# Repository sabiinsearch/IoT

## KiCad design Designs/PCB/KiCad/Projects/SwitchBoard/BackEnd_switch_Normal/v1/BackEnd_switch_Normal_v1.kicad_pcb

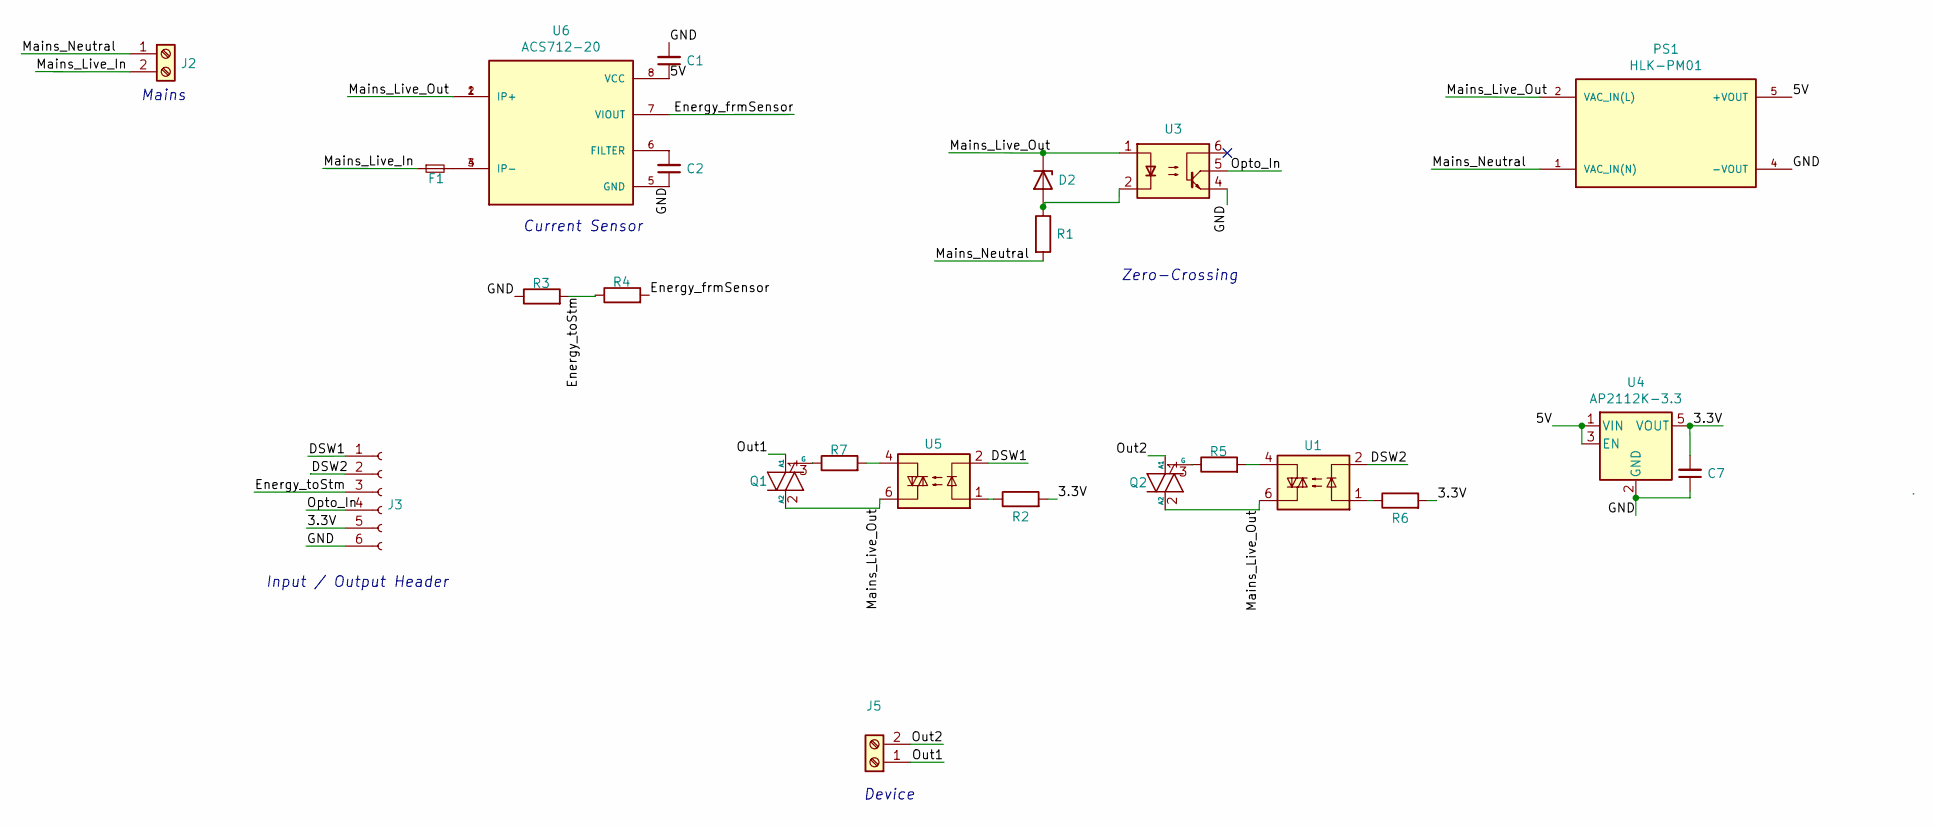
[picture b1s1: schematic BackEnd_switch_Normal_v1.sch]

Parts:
C1: 100nf; C_0805_2012Metric_Pad1.18x1.45mm_HandSolder
C2: 1nf; C_0805_2012Metric_Pad1.18x1.45mm_HandSolder
C7: 2.2uf; C_0805_2012Metric_Pad1.18x1.45mm_HandSolder
D2: IN14007; D_0805
F1: Fuse_Small; Fuse_TE5_Littlefuse-395Series
J2: Screw_Terminal_01x02; TerminalBlock_Phoenix_MKDS-1,5-2_1x02_P5.00mm_Horizontal
J3: Conn_01x06_Female; PinHeader_1x06_P2.54mm_Vertical
J5: Screw_Terminal_01x02; TerminalBlock_Phoenix_MKDS-1,5-2-5.08_1x02_P5.08mm_Horizont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
PS1: HLK-PM01; 277
Q1, Q2: BT136-500; BT136S
R1: 220K; R_0805_HandSoldering
R2, R6: 100E; R_0805_2012Metric
R3, R4: 5K; R_0805_2012Metric
R5, R7: 470E; R_0805_2012Metric
U1, U5: MOC3021; OPTOCOUPLER_SMD
U3: 4N35; DIP-6_W8.89mm_SMDSocket_LongPads
U4: AP2112K-3.3; SOT-23-5_HandSoldering
U6: ACS712-20; ACS712_20; PARTREV 19

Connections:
/3.3V: C7.2, J3.5, R2.2, R6.2, U4.5 (VOUT)
/5V: C1.1, PS1.5 (+VOUT), U4.1 (VIN), U4.3 (EN), U6.8 (VCC)
/DSW1: J3.1, U5.2
/DSW2: J3.2, U1.2
/Energy_frmSensor: R4.2, U6.7 (VIOUT)
/Energy_toStm: J3.3, R3.2, R4.1
/GND: C1.2, C2.1, C7.1, J3.6, PS1.4 (-VOUT), R3.1, U3.4, U4.2 (GND), U6.5 (GND)
/Mains_Live_In: F1.1, J2.2
/Mains_Live_Out: D2.1 (K), PS1.2 (VAC_IN(L)), Q1.2 (A2), Q2.2 (A2), U1.6, U3.1, U5.6, U6.1 (IP+), U6.2 (IP+)
/Mains_Neutral: J2.1, PS1.1 (VAC_IN(N)), R1.2
/Opto_In: J3.4, U3.5
/Out1: J5.1, Q1.1 (A1)
/Out2: J5.2, Q2.1 (A1)
unnamed: C2.2, U6.6 (FILTER)
unnamed: D2.2 (A), R1.1, U3.2
unnamed: F1.2, U6.3 (IP-), U6.4 (IP-)
unnamed: Q1.3 (G), R7.1
unnamed: Q2.3 (G), R5.1
unnamed: R2.1, U5.1
unnamed: R5.2, U1.4
unnamed: R6.1, U1.1
unnamed: R7.2, U5.4

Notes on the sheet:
Mains
Current Sensor
Zero-Crossing
Input / Output Header
Device

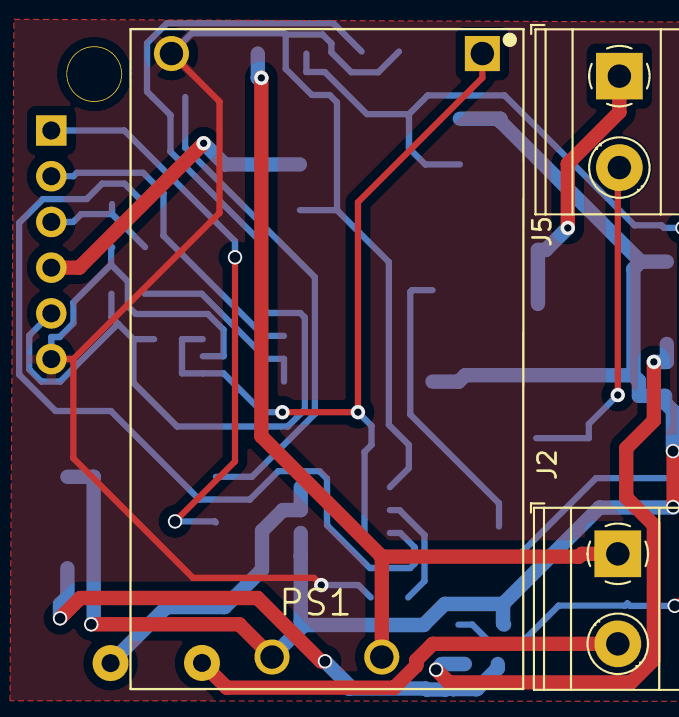
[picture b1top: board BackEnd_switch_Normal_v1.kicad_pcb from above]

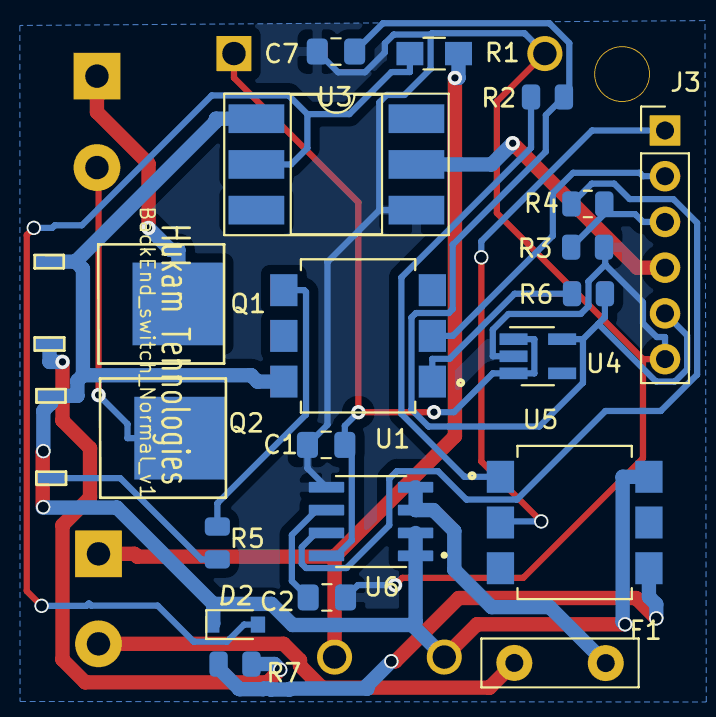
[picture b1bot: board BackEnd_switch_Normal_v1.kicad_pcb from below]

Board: 2 copper layers, 24 parts (20 on the bottom side), 22 nets.

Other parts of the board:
M2: MountingHole_2.1mm; MountingHole_2.5mm

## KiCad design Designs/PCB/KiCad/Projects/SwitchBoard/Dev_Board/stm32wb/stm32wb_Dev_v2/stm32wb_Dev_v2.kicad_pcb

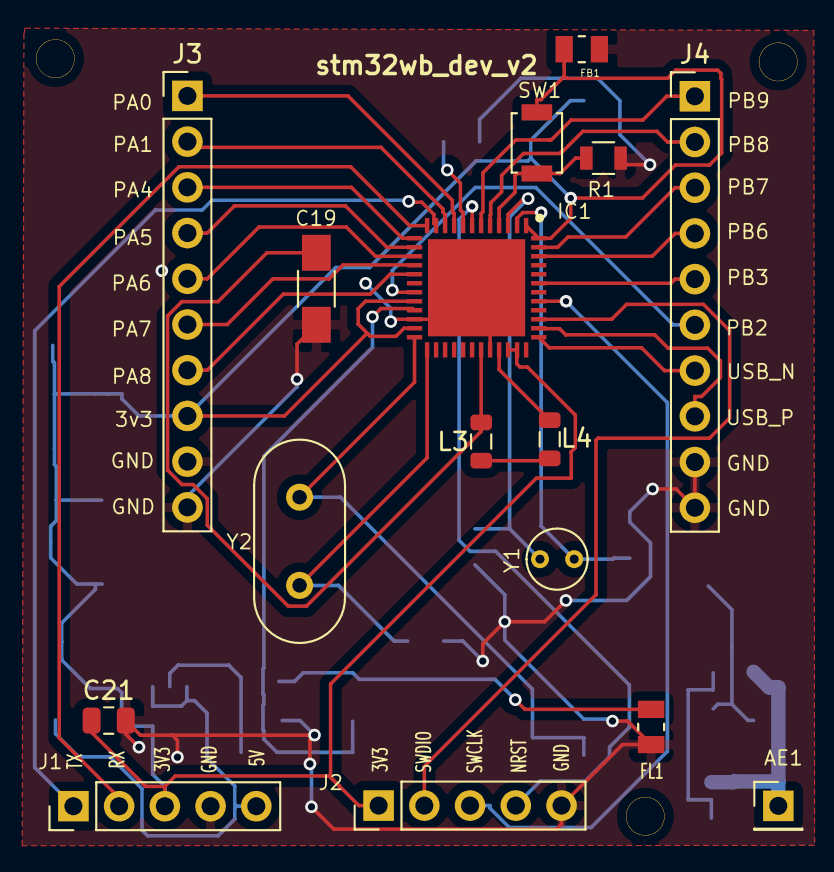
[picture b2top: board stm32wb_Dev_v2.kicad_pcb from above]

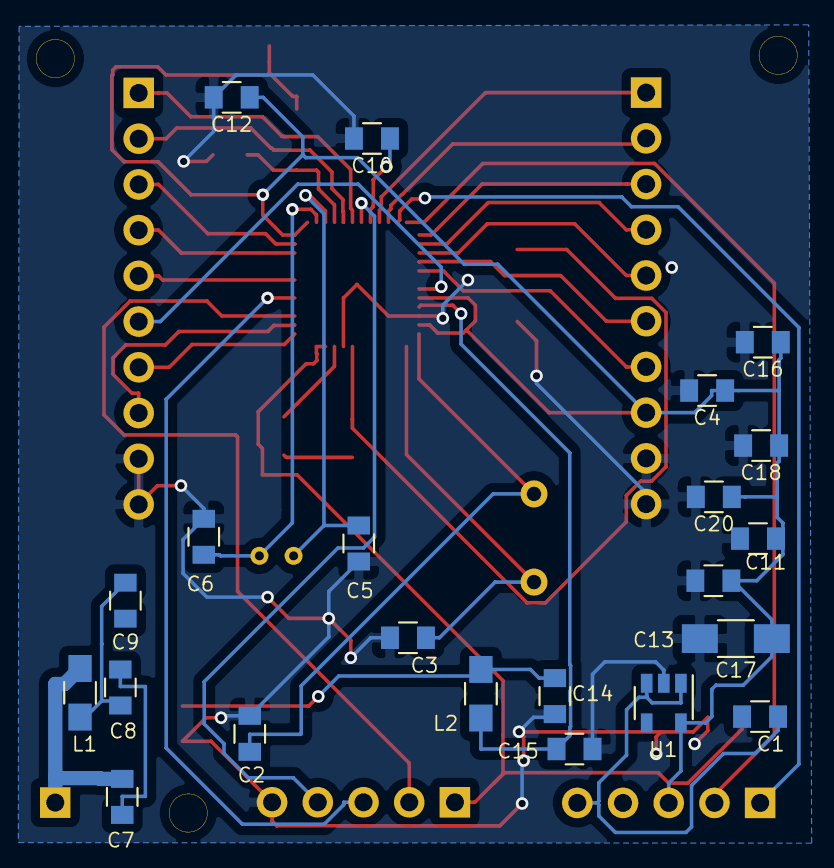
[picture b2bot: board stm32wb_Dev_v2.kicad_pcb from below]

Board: 2 copper layers, 41 parts (22 on the bottom side), 37 nets.

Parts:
AE1: Antenna; Pin_Header_Straight_1x01_Pitch2.54mm
C1, C4, C10, C12, C13, C16, C20: 100nf; C_0805
C2, C3: 22p; C_0805
C5, C6: 15pf; C_0805
C7: 1.2p; C_0805
C8: NM; C_0805
C9: 10nf; C_0805
C11, C18: 100p; C_0805
C14: 0.3p; C_0805
C15: 0.8p; C_0805
C17, C19: 4.7uf; C_1206_HandSoldering
C21: 100nf; C_0805_2012Metric
FB1: FCM1608KF-601T03; RESC0805X60N
FL1: LFB182G45CGFD436; RESC0805X60N
IC1: STM32WB55CEU6; QFN50P700X700X65-49N-D
J1, J2: Conn_01x05_Female; Pin_Header_Straight_1x05_Pitch2.54mm
J3, J4: Conn_01x10_Female; PinHeader_1x10_P2.54mm_Vertical
L1: 3.6nH; L_0805_HandSoldering
L2: 2.7nH; L_0805_HandSoldering
L3, L4: 10nH; L_0805_2012Metric
M1, M2, M3: MountingHole_2.1mm; MountingHole1.5mm
R1: 10K; R_0805
SW1: SW_Push; SW_SPST_B3U-1000P
U1: AP2112K-3.3; SOT-23-5
Y1: 32.768KHz; Crystal_Round_d3.0mm_Vertical
Y2: 32MHz; Crystal_HC18-U_Vertical

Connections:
/3V3: C4.1, C11.1, C12.1, C13.1, C16.1, C17.1, C18.1, C20.1, C21.1, FB1.2, IC1.1, IC1.20, IC1.23, IC1.34, IC1.35, IC1.48, J1.3, J2.1, J3.8, SW1.1, U1.5
/5V: C1.1, J1.5, U1.1, U1.3
/GND: C1.2, C2.2, C3.2, C4.2, C5.1, C6.1, C10.2, C11.2, C12.2, C13.2, C14.2, C15.2, C16.2, C17.2, C18.2, C19.2, C20.2, C21.2, FB1.1, FL1.2, IC1.22, IC1.32, IC1.49, J1.4, J2.5, J3.9, J3.10, J4.9, J4.10, R1.2, U1.2
/NRST: IC1.7, J2.4
/OSC_IN: C3.1, IC1.25, Y2.2
/OSC_OUT: C2.1, IC1.24, Y2.1
/PA0: IC1.9, J3.1
/PA1: IC1.10, J3.2
/PA4: IC1.13, J3.3
/PA5: IC1.14, J3.4
/PA6: IC1.15, J3.5
/PA7: IC1.16, J3.6
/PA8: IC1.17, J3.7
/PB2: IC1.19, J4.6
/PB3: IC1.43, J4.5
/PB6: IC1.46, J4.4
/PB7: IC1.47, J4.3
/PB8: IC1.5, J4.2
/PB9: IC1.6, J4.1
/PC14: C6.2, IC1.2, Y1.2
/PC15: C5.2, IC1.3, Y1.1
/SWCLK: IC1.41, J2.3
/SWDIO: IC1.39, J2.2
/UART_RX: IC1.12, J1.2
/UART_TX: IC1.11, J1.1
/USB_N: IC1.37, J4.7
/USB_P: IC1.38, J4.8
unnamed: AE1.1, C7.1, L1.1
unnamed: C7.2, C8.2
unnamed: C8.1, C9.1, L1.2
unnamed: C10.1, IC1.8
unnamed: C14.1, FL1.1, L2.1
unnamed: C15.1, IC1.21, L2.2
unnamed: C19.1, IC1.31, L3.2
unnamed: IC1.4, R1.1, SW1.2
unnamed: IC1.33, L4.1
unnamed: L3.1, L4.2

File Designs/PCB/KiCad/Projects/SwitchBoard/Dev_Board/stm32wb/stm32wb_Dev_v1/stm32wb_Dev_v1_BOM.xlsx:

Id | Designator | Value | Package | Quantity | Supplier and ref
1 | FL1 | LFB182G45CGFD436 | FIL_LFB182G45CGFD436 | 1
2 | IC1 | STM32WB55CEU6 | QFN50P700X700X65-49N-D | 1
3 | C19,C17 | 4.7uf | C_1206_HandSoldering | 2
4 | AE1 | Antenna | Pin_Header_Straight_1x01_Pitch2.54mm | 1
5 | C1,C4,C10,C12,C13,C16,C20 | 100nf | C_0805 | 7
6 | C2,C3 | 22p | C_0805 | 2
7 | C5,C6 | 10p | C_0805 | 2
8 | C7 | 1.2p | C_0805 | 1
9 | C8 | NM | C_0805 | 1
10 | C9 | 10nf | C_0805 | 1 |  |  |  | Available
11 | C11,C18 | 100p | C_0805 | 2 |  |  |  | Not Available
12 | C14 | 0.3p | C_0805 | 1
13 | C15 | 0.8p | C_0805 | 1
14 | J1,J2 | Conn_01x05_Female | Pin_Header_Straight_1x05_Pitch2.54mm | 2
15 | J3,J4 | Headers_01x12 | Pin_Header_Straight_1x12_Pitch2.54mm | 2
16 | L1 | 3.6nH | L_0805_HandSoldering | 1
17 | L2 | 2.7nH | L_0805_HandSoldering | 1
18 | L3 | 10nH | L_0805_HandSoldering | 1
19 | L4 | 10uH | L_0805_HandSoldering | 1
20 | R1 | 10K | R_0805 | 1
21 | SW1 | SW_Push | SW_SPST_B3U-1000P | 1
22 | U1 | AP2112K-3.3 | SOT-23-5 | 1
23 | Y1 | 32.768KHz | Crystal_Round_d3.0mm_Vertical | 1
24 | Y2 | 32MHz | Crystal_HC18-U_Vertical | 1

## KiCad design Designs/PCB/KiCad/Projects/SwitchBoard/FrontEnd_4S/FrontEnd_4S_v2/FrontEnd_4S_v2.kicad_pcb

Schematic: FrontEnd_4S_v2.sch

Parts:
AE1: Antenna; Anntenna
C1, C2, C8, C9, C10, C11: 100 nf; C_0805
C3: 1.0uf; C_0805
C4, C5: 10pf; C_0805
C6, C7: 20pf; C_0805
C12, C13, C14, C15: 10uf; C_0805
D1, D2, D3, D4, D5, D6: LED; D_0805
D7: LED_RGB; LED_IN-P55TATRGB
J1: Conn_01x06_Female; Pin_Header_Straight_1x06_Pitch2.54mm
J2: Header_Out_01x08; Pin_Header_Straight_1x08_Pitch2.54mm
R1, R3, R4, R5, R6, R7, R8: 510 R; R_0805
R2: 10K; R_0805
SW1: SW_Push; SW_DIP_x1_W7.62mm_Slide_Copal_CHS-B
T1, T2, T3, T4: Touch_Pad
U1: APK2112.K-3.3; SOT-23-5
U2: STM32; STM32(LQFP48)
U3: LoRa
U4, U5, U6, U7: TTP223; SOT-23-6
Y1: 32.768K; Crystal_HC49-4H_Vertical
Y2: 32Mhz; Crystal_HC49-4H_Vertical

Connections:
/5V: C1.2, J2.2
/DIO0: U2.10 (PA0), U3.5 (DIO0)
/DSW_1: J2.8, R4.2, U2.11 (PA1)
/DSW_2: J2.7, R6.2, U2.21 (PB10)
/DSW_3: J2.6, R7.2, U2.22 (PB11)
/DSW_4: J2.5, R5.2, U2.25 (PB12)
/Energy: J2.4, U2.38 (PA15)
/GND: C1.1, C2.1, C3.1, C4.2, C5.2, C6.2, C7.2, C8.1, C9.1, C10.1, C11.1, C12.1, C13.1, C14.1, C15.1, D1.1 (K), D2.1 (K), D3.1 (K), D4.1 (K), D5.1 (K), D6.1 (K), J1.1, J2.1, R8.2, SW1.1, U2.8 (VSSA), U2.20 (PB2/BOOT1), U2.23 (VSS_1), U2.35 (VSS_2), U2.44 (BOOT0), U2.47 (VSS_3), U3.2 (GND), U3.9 (GND), U3.16 (GND), U4.2 (VSS), U5.2 (VSS), U6.2 (VSS), U7.2 (VSS)
/MISO: U2.16 (PA6), U3.13 (MISO)
/MOSI: U2.17 (PA7), U3.14 (MOSI)
/NSS: U2.14 (PA4), U3.15 (NSS)
/OSCIN: C6.1, U2.5 (OSCIN), Y2.1
/OSCOUT: C7.1, U2.6 (OSCOUT), Y2.2
/Opto_IN: J2.3, U2.12 (PA2)
/PC14: C4.1, U2.3 (PC14), Y1.1
/PC15: C5.1, U2.4 (PC15), Y1.2
/RESET: C3.2, R2.2, SW1.2, U2.7 (NRST)
/RX0: J1.6, U2.31 (PA10)
/Reset_Lora: U2.2 (PC13), U3.4 (Reset)
/SCK: U2.15 (PA5), U3.12 (SCK)
/SWCLK: J1.2, U2.37 (SWCLK)
/SWIO: J1.3, U2.34 (SWIO)
/TX0: J1.5, U2.30 (PA9)
/Touch_1: U2.39 (PB3), U4.1 (Q)
/Touch_2: U2.40 (PB4), U5.1 (Q)
/Touch_3: U2.41 (PB5), U6.1 (Q)
/Touch_4: U2.18 (PB0), U7.1 (Q)
/VCC3V3: C2.2, C8.2, C9.2, C10.2, C11.2, C12.2, C13.2, C14.2, C15.2, J1.4, R1.2, R2.1, U2.1 (VBAT), U2.9 (VDDA), U2.24 (VDD_1), U2.36 (VDD_2), U2.48 (VDD_3), U3.3 (3.3_V), U4.5 (VDD), U5.5 (VDD), U6.5 (VDD), U7.5 (VDD)
unnamed: AE1.1, U3.1 (Ant)
unnamed: D1.2 (A), R1.1
unnamed: D2.2 (A), R3.1
unnamed: D3.2 (A), R4.1
unnamed: D4.2 (A), R5.1
unnamed: D5.2 (A), R6.1
unnamed: D6.2 (A), R7.1
unnamed: D7.1 (RK), D7.2 (GK), D7.3 (BK), R8.1
unnamed: D7.4 (BA), U2.29 (PA8)
unnamed: D7.5 (GA), U2.28 (PB15)
unnamed: D7.6 (RA), U2.27 (PB14)
unnamed: R3.2, U2.33 (PA12)
unnamed: T1.1, U4.3 (I)
unnamed: T2.1, U5.3 (I)
unnamed: T3.1, U6.3 (I)
unnamed: T4.1, U7.3 (I)

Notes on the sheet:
Programming Headers
Power
Reset
LoRa Module
STM & Crystals
Touch Pads
Input / Output Headers
ST-Link Header

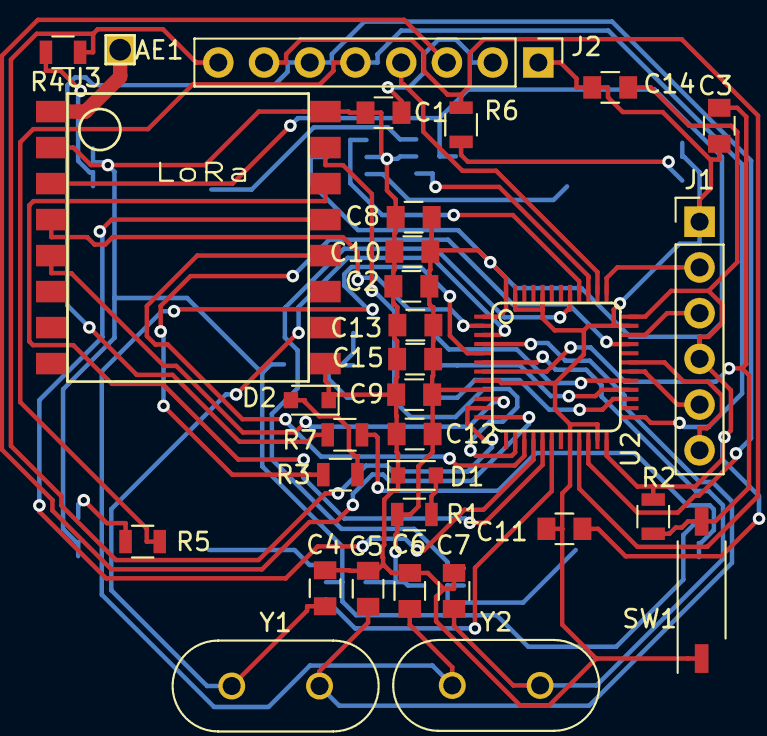
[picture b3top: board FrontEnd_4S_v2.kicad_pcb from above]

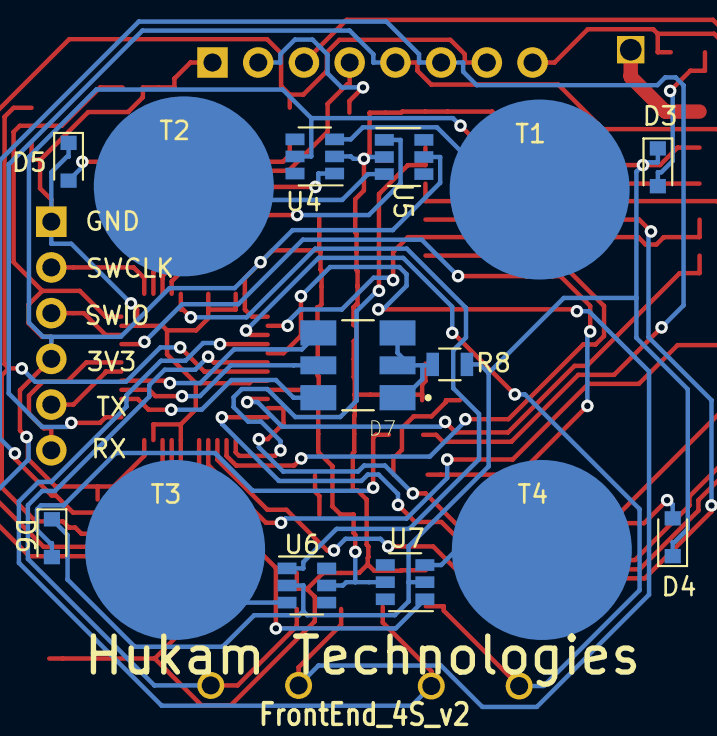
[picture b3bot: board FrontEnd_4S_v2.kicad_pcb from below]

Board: 2 copper layers, 46 parts (14 on the bottom side), 44 nets.

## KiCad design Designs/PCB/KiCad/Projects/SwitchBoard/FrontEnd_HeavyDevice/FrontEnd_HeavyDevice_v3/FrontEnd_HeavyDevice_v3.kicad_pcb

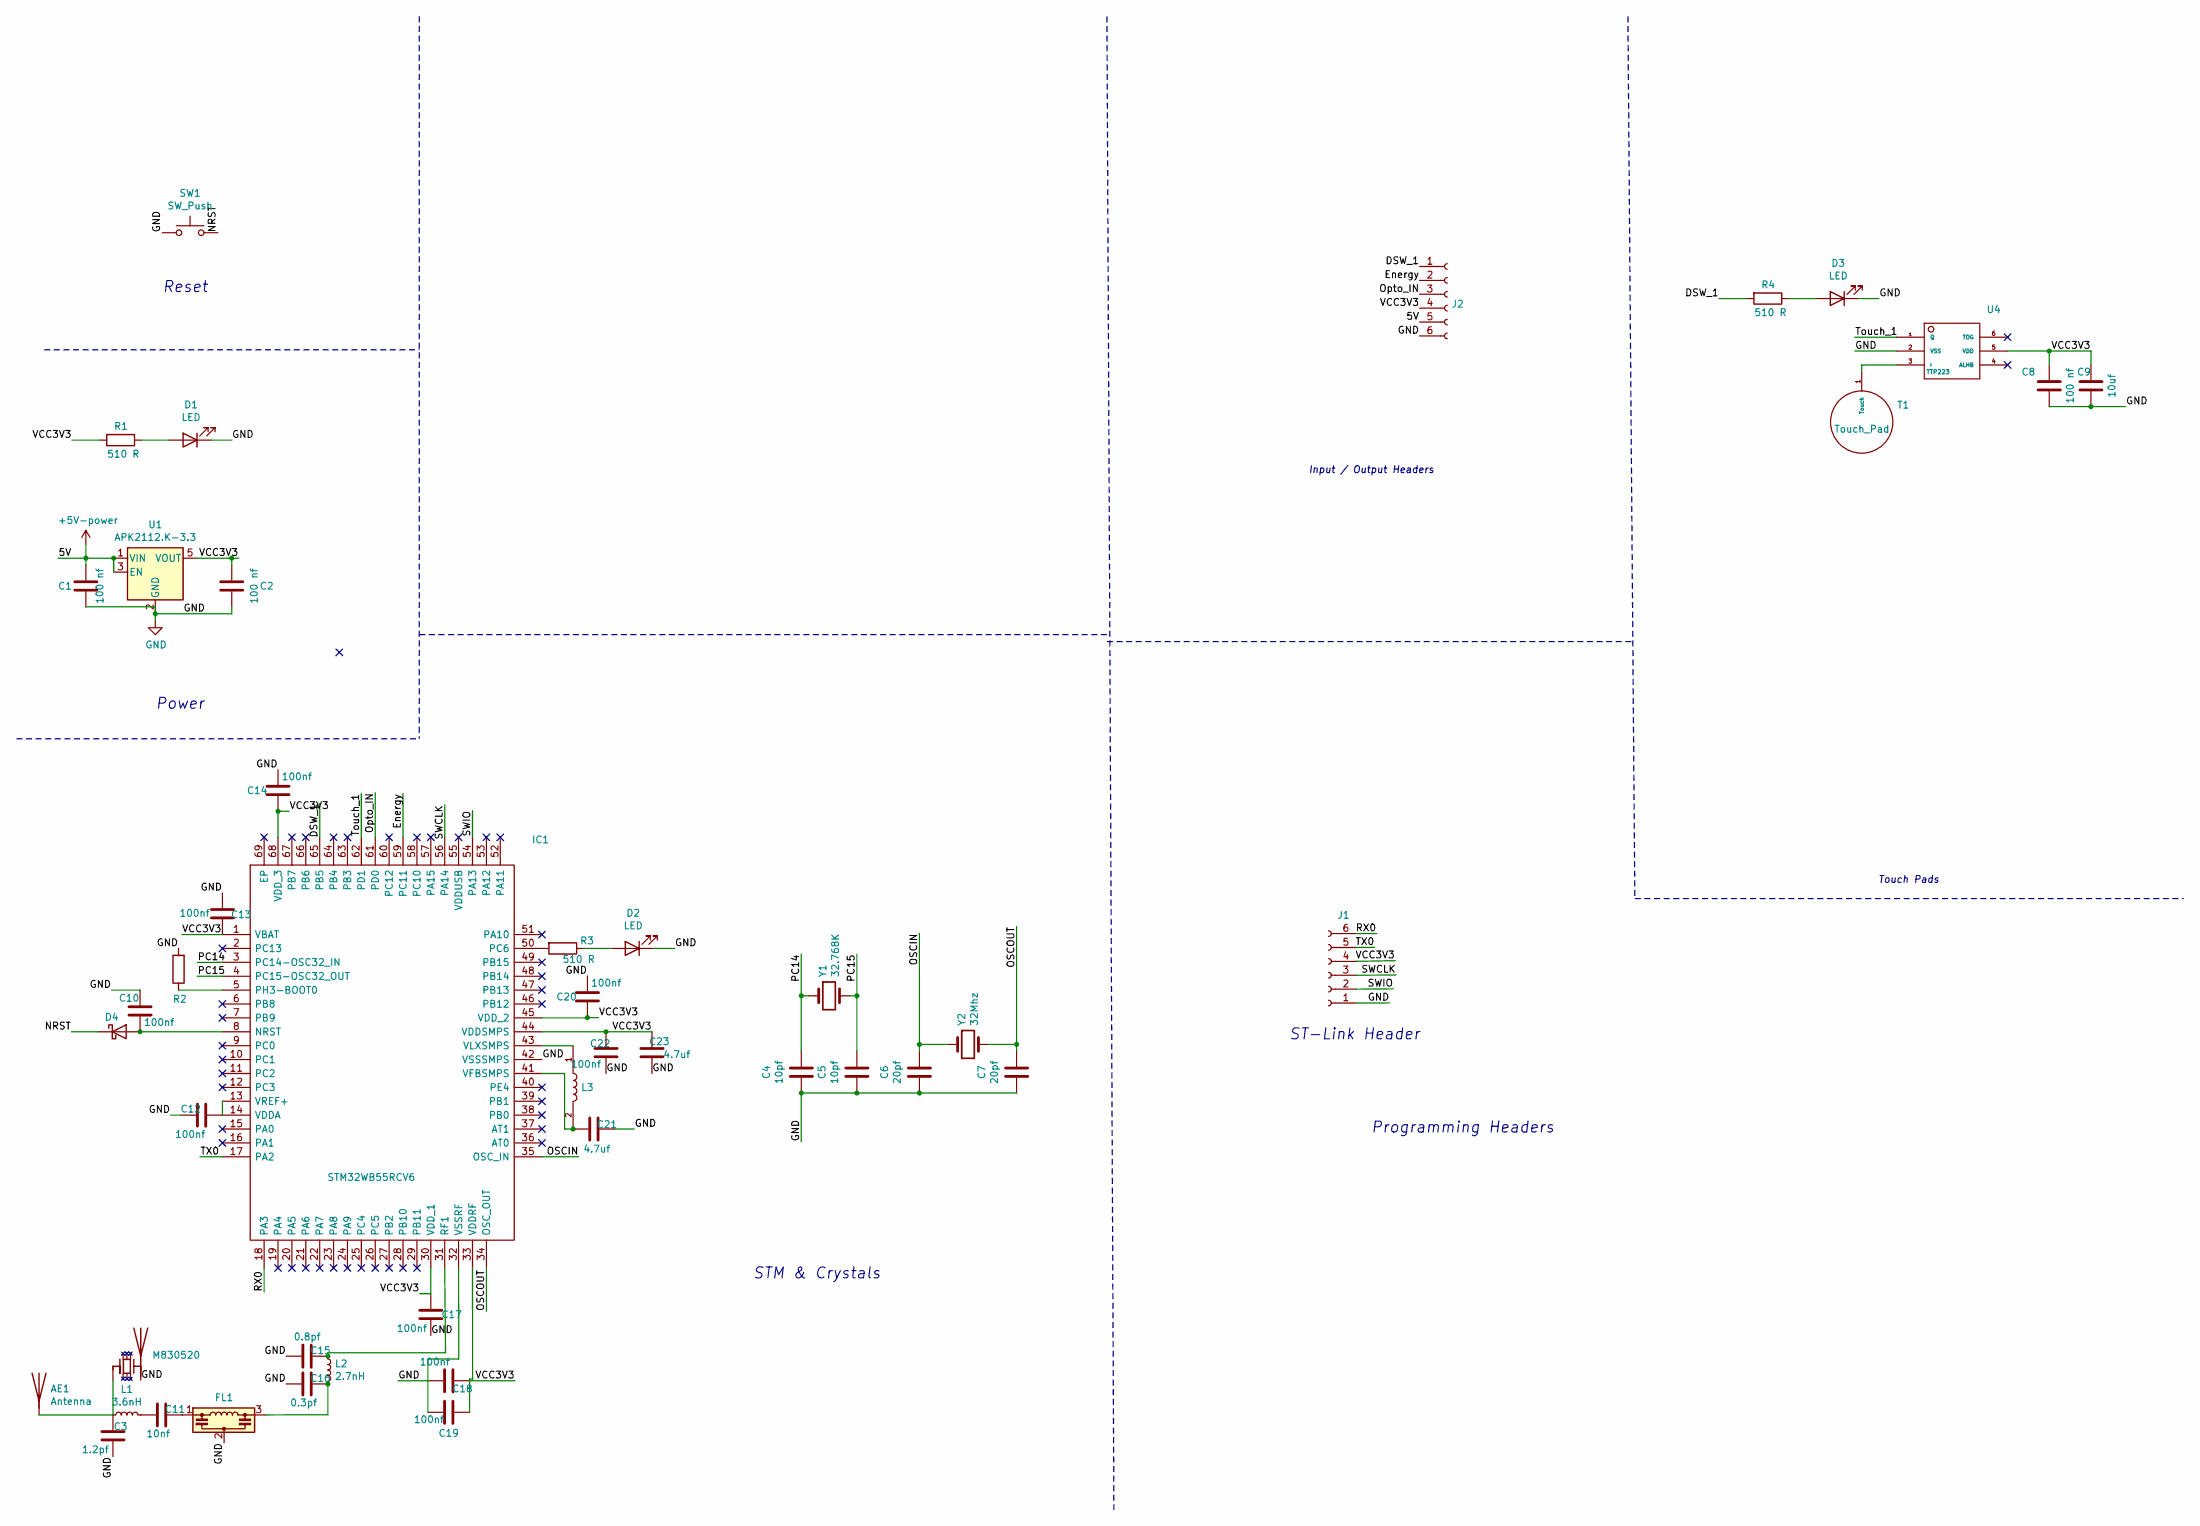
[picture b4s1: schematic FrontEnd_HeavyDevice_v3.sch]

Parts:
AE1: Antenna; Anntenna
AE2: M830520
C1, C2, C8: 100 nf; C_0805_2012Metric
C3: 1.2pf; C_0805_2012Metric
C4, C5: 10pf; C_0805_2012Metric
C6, C7: 20pf; C_0805_2012Metric
C9: 10uf; C_0805_2012Metric
C10, C12, C13, C14, C17, C18, C19, C20, C22: 100nf; C_0805_2012Metric
C11: 10nf; C_0805_2012Metric
C15: 0.8pf; C_0805_2012Metric
C16: 0.3pf; C_0805_2012Metric
C21, C23: 4.7uf; C_0805_2012Metric
D1, D3: LED; D_0805
D2: LED; D_0805_2012Metric_Pad1.15x1.40mm_HandSolder
D4: BAT54KFILM; D_0805_2012Metric
FL1: LFB182G45CGFD436; FIL_LFB182G45CGFD436
IC1: STM32WB55RCV6; STM32WBRGV7; Manufacturer_Part_Number STM32WB55RCV6; Mouser Part Number 511-STM32WB55RCV6
J1: Conn_01x06_Female; Pin_Header_Straight_1x06_Pitch2.54mm
J2: Conn_01x06_Female; PinHeader_1x06_P2.54mm_Vertical
L1: 3.6nH; L_0805_2012Metric_Pad1.05x1.20mm_HandSolder
L2: 2.7nH; L_0805_2012Metric_Pad1.05x1.20mm_HandSolder
L3: 10uH; Fixed_Inductor_0805
R1, R3, R4: 510 R; R_0805_2012Metric_Pad1.20x1.40mm_HandSolder
R2: 10K; R_0805_2012Metric_Pad1.20x1.40mm_HandSolder
SW1: SW_Push; SW_DIP_SPSTx01_Slide_9.78x4.72mm_W8.61mm_P2.54mm
T1: Touch_Pad
U1: APK2112.K-3.3; SOT-23-5
U4: TTP223; TTP223_SOT95
Y1: 32.768K; Crystal_HC49-4H_Vertical
Y2: 32Mhz; Crystal_HC49-4H_Vertical

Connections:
/5V: C1.2, J2.5, U1.1 (VIN), U1.3 (EN)
/DSW_1: IC1.65 (PB5), J2.1, R4.2
/Energy: IC1.59 (PC11), J2.2
/GND: AE2.2 (PCB_Trace), C1.1, C2.1, C3.1, C4.2, C5.2, C6.2, C7.2, C8.1, C9.1, C10.2, C12.1, C13.1, C14.2, C15.2, C16.2, C17.2, C18.2, C20.2, C21.2, C22.1, C23.1, D1.1 (K), D2.1 (K), D3.1 (K), FL1.2, IC1.42 (VSSSMPS), J1.1, J2.6, R2.2, SW1.1, U1.2 (GND), U4.2 (VSS)
/NRST: D4.1 (K), SW1.2
/OSCIN: C6.1, IC1.35 (OSC_IN), Y2.1
/OSCOUT: C7.1, IC1.34 (OSC_OUT), Y2.2
/Opto_IN: IC1.61 (PD0), J2.3
/PC14: C4.1, IC1.3 (PC14-OSC32_IN), Y1.1
/PC15: C5.1, IC1.4 (PC15-OSC32_OUT), Y1.2
/RX0: IC1.18 (PA3), J1.6
/SWCLK: IC1.56 (PA14), J1.3
/SWIO: IC1.54 (PA13), J1.2
/TX0: IC1.17 (PA2), J1.5
/Touch_1: IC1.62 (PD1), U4.1 (Q)
/VCC3V3: C2.2, C8.2, C9.2, C13.2, C14.1, C17.1, C18.1, C20.1, C22.2, C23.2, IC1.1 (VBAT), IC1.30 (VDD_1), IC1.44 (VDDSMPS), IC1.45 (VDD_2), IC1.68 (VDD_3), J1.4, J2.4, R1.2, U1.5 (VOUT), U4.5 (VDD)
unnamed: AE1.1, AE2.1 (FEED), C3.2, L1.1
unnamed: C10.1, D4.2 (A), IC1.8 (NRST)
unnamed: C11.1, FL1.1
unnamed: C11.2, L1.2
unnamed: C12.2, IC1.13 (VREF+), IC1.14 (VDDA)
unnamed: C15.1, IC1.31 (RF1), L2.1
unnamed: C16.1, FL1.3, L2.2
unnamed: C19.1, IC1.33 (VDDRF)
unnamed: C19.2, IC1.32 (VSSRF)
unnamed: C21.1, IC1.41 (VFBSMPS), L3.2
unnamed: D1.2 (A), R1.1
unnamed: D2.2 (A), R3.1
unnamed: D3.2 (A), R4.1
unnamed: IC1.5 (PH3-BOOT0), R2.1
unnamed: IC1.43 (VLXSMPS), L3.1
unnamed: IC1.50 (PC6), R3.2
unnamed: T1.1, U4.3 (I)

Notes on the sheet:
Programming Headers
Reset
STM & Crystals
Touch Pads
Input / Output Headers
ST-Link Header
Power

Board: 2 copper layers, 46 parts (4 on the bottom side), 33 nets, no tracks yet.
